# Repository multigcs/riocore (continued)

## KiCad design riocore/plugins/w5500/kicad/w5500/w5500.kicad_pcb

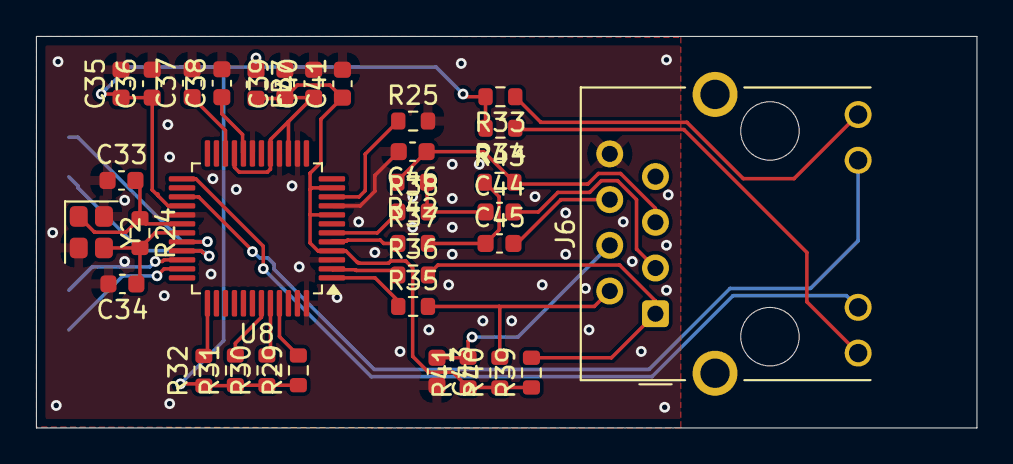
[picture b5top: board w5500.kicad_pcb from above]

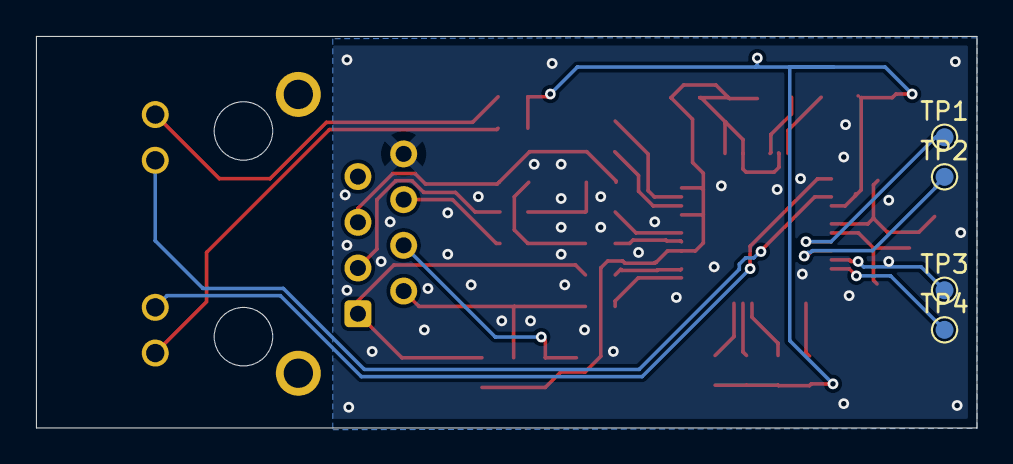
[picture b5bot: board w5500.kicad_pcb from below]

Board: 2 copper layers, 52.2 x 21.8 mm, 38 parts (4 on the bottom side), 32 nets.

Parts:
C33, C34: 18pF; C_0603_1608Metric
C35, C39: 10uF/6.3V; C_0603_1608Metric
C36, C40, C41: 0.1uF; C_0603_1608Metric
C37, C46: 10nF; C_0603_1608Metric
C38: 4.7uF; C_0603_1608Metric
C43: 22nF; C_0603_1608Metric
C44, C45: 6.8nF; C_0603_1608Metric
FB7: FB_100R_3A; L_0603_1608Metric
J6: RJ45_Pulse_J0011D21BNL; RJ45_Hanrun_HR911105A_Horizontal
R24: 1M; R_0603_1608Metric
R25: 12.4K; R_0603_1608Metric
R29, R30, R31, R32: 10K; R_0603_1608Metric
R33, R34: 330R; R_0603_1608Metric
R35, R36, R37, R38: 0R; R_0603_1608Metric
R39, R40, R42, R43: 49.9R; R_0603_1608Metric
R41: 10R; R_0603_1608Metric
TP1, TP2, TP3, TP4: TestPoint; TestPoint_Pad_D1.0mm
U8: W5500; LQFP-48_7x7mm_P0.5mm
Y2: Crystal_25MHz; Crystal_SMD_2520-4Pin_2.5x2.0mm

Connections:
+3V3: C35.1, C36.1, FB7.1, R29.1, R30.1, R31.1, R32.1, R33.2, R34.2, U8.28 (VDD)
/3V3_ADD: C39.1, C40.1, C41.1, FB7.2, R39.1, R40.1, R41.1, U8.4 (AVDD), U8.8 (AVDD), U8.11 (AVDD), U8.15 (AVDD), U8.17 (AVDD), U8.21 (AVDD)
/LED_GRN: J6.10, U8.25 (LINKLED)
/LED_YEL: J6.11, U8.27 (ACTLED)
/miso: TP3.1, U8.34 (MISO)
/mosi: TP4.1, U8.35 (MOSI)
/rst: R32.2, U8.37 (~RST)
/sclk: TP2.1, U8.33 (SCLK)
/sel: TP1.1, U8.32 (~SCS)
GND: C33.1, C34.2, C35.2, C36.2, C37.2, C38.2, C39.2, C40.2, C41.2, C43.2, C46.2, J6.8 (SH), R25.2, U8.3 (AGND), U8.9 (AGND), U8.14 (AGND), U8.16 (AGND), U8.19 (AGND), U8.29 (GND), U8.48 (AGND), Y2.2, Y2.4
unnamed: C44.1, R38.2, R42.1
unnamed: C45.1, R37.2, R43.1
unnamed: J6.9, R34.1
unnamed: J6.12, R33.1
unnamed: C46.1, J6.5 (RCT), R42.2, R43.2
unnamed: C44.2, J6.3 (RD+)
unnamed: C45.2, J6.6 (RD-)
unnamed: C43.1, J6.4 (TCT), R41.2
unnamed: J6.1 (TD+), R36.2, R39.2
unnamed: J6.2 (TD-), R35.2, R40.2
unnamed: C37.1, U8.22 (1V2O)
unnamed: R25.1, U8.10 (EXRES1)
unnamed: R29.2, U8.45 (PMODE0)
unnamed: R30.2, U8.44 (PMODE1)
unnamed: R31.2, U8.43 (PMODE2)
unnamed: R37.1, U8.5 (RXN)
unnamed: R38.1, U8.6 (RXP)
unnamed: C38.1, U8.20 (TOCAP)
unnamed: R35.1, U8.1 (TXN)
unnamed: R36.1, U8.2 (TXP)
unnamed: C33.2, R24.1, U8.30 (XI/CLKIN), Y2.1
unnamed: C34.1, R24.2, U8.31 (XO), Y2.3

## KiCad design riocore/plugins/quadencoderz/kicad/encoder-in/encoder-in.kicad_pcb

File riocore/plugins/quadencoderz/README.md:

# quadencoderz

**quadencoder with index pin**

usable as spindle-encoder for rigid tapping and thread cutting.  It is critical that your position-scale and QUAD_TYPE match, see the details in the description for QUAD_TYPE

* Keywords: feedback encoder rotary linear glassscale  index
* NEEDS: fpga

## Pins:
*FPGA-pins*
### a:

 * direction: input
 * pull: up

### b:

 * direction: input
 * pull: up

### z:
index pin

 * direction: input
 * pull: up

## Options:
*user-options*
### name:
name of this plugin instance

 * type: str
 * default: 

### image:
hardware type

 * type: imgselect
 * default: generic

### quad_type:
The count from the encoder will be bitshifted by the value of QUAD_TYPE.
Use 0 for 4x mode.  The position-scale should match.
For examle if you have a 600 CPR encoder 4x mode will give you 2400 PPR and your scale should be set to 2400.

 * type: int
 * min: 0
 * max: 4
 * default: 2

### rps_sum:
number of collected values before calculate the rps value

 * type: int
 * min: 0
 * max: 100
 * default: 10

## Signals:
*signals/pins in LinuxCNC*
### indexenable:

 * type: bit
 * direction: inout

### indexout:

 * type: bit
 * direction: input

### nocntreset:
set counter to zero on index in hardware

 * type: bit
 * direction: output

### position:
position feedback in steps

 * type: float
 * direction: input

### rps:
calculates revolutions per second

 * type: float
 * direction: input

### rpm:
calculates revolutions per minute

 * type: float
 * direction: input

## Interfaces:
*transport layer*
### indexenable:

 * size: 1 bit
 * direction: output

### indexout:

 * size: 1 bit
 * direction: input

### position:

 * size: 32 bit
 * direction: input

### nocntreset:

 * size: 1 bit
 * direction: output

## Verilogs:
 * [quadencoderz.v](quadencoderz.v)

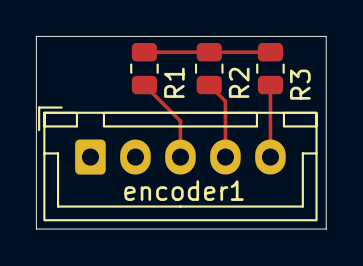
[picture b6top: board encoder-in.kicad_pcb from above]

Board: 2 copper layers, 16.1 x 10.7 mm, 4 parts (0 on the bottom side), 4 nets.

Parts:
R1, R2, R3: 10k; R_0805_2012Metric
encoder1: Conn_01x05; JST_XH_B5B-XH-A_1x05_P2.50mm_Vertical

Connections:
+3V3: R1.2, R2.2, R3.2
/a: R1.1, encoder1.3
/b: R2.1, encoder1.4
/z: R3.1, encoder1.5

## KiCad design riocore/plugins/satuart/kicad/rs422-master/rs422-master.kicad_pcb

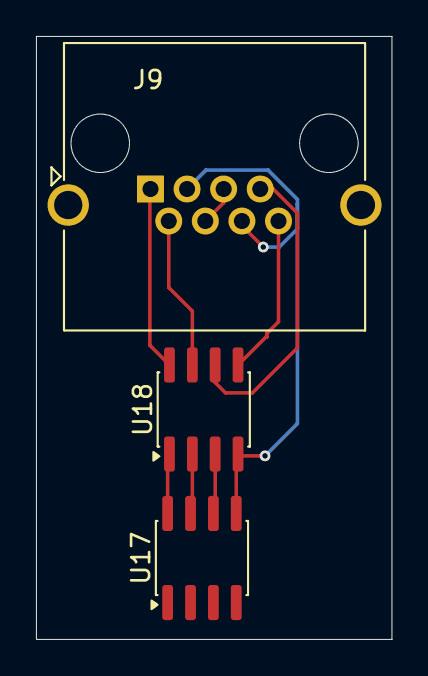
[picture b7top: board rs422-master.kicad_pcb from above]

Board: 2 copper layers, 19.8 x 33.5 mm, 3 parts (0 on the bottom side), 9 nets.

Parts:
J9: RJ45; RJ45_Amphenol_RJHSE5380
U17: ADuM1201BR; SOIC-8_3.9x4.9mm_P1.27mm
U18: ADM3488ExR; SOIC-8_3.9x4.9mm_P1.27mm

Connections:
F_5V: U17.8 (VDD2), U18.1 (VCC)
F_24V: J9.4, J9.5
F_GND: J9.3, J9.6, U17.5 (GND2), U18.4 (GND)
unnamed: U17.7 (VIA), U18.2 (RO)
unnamed: U17.6 (VOB), U18.3 (DI)
unnamed: J9.1, U18.8 (A)
unnamed: J9.2, U18.7 (B)
unnamed: J9.8, U18.5 (Y)
unnamed: J9.7, U18.6 (Z)

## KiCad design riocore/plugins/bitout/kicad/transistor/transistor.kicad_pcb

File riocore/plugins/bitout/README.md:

# bitout

**singe bit output pin**

to control relay, leds, valves, ....

* Keywords: led relais relay valve lamp motor magnet
* NEEDS: fpga

## Pins:
*FPGA-pins*
### bit:

 * direction: output

## Options:
*user-options*
### name:
name of this plugin instance

 * type: str
 * default: 

### image:
hardware type

 * type: imgselect
 * default: generic

## Signals:
*signals/pins in LinuxCNC*
### bit:

 * type: bit
 * direction: output

## Interfaces:
*transport layer*
### bit:

 * size: 1 bit
 * direction: output

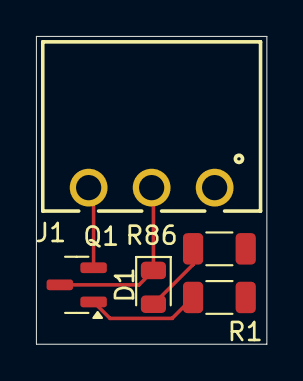
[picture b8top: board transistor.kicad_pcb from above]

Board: 2 copper layers, 12.8 x 17.1 mm, 5 parts (0 on the bottom side), 4 nets.

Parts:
D1: LED; LED_0805_2012Metric
J1: bit_out; 691322110003
Q1: BC817; SOT-23
R1: 1k; R_1206_3216Metric
R86: 560; R_1206_3216Metric

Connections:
GND: J1.3, Q1.2 (E)
unnamed: D1.2 (A), R86.2
unnamed: D1.1 (K), J1.2, Q1.3 (C)
unnamed: Q1.1 (B), R1.2

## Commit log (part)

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2026-04-25 kicad: adding offsets
2026-04-25 kicad: using rendered images
2026-04-25 flow: fixing generic image view
2026-04-25 flow: icons
2026-04-25 kicad: adding pico module / encoder
2026-04-25 kicad: per board filtering
2026-04-27 kicad: stepstick module
2026-04-27 kicad: renew some uuids
2026-04-27 kicad: spi-connector module
2026-04-27 kicad: encoder-in module
2026-04-27 some changes
2026-04-27 some fixes
2026-04-29 kicad: ecp5 tests
2026-05-06 flow: fixing edge delete
2026-05-11 modifiers: add only used verilogs
2026-05-11 ISE: using single verilog files and xst-file
2026-05-11 ISE: experimental cpld support / adding XC9536XL board
2026-05-11 ruff: activate B006
2026-05-11 ruff: activate PLR1733, RUF100
2026-05-11 ruff: activate PYI061,RUF059,PLR1714
2026-05-11 ruff: activate RET501,RET502
2026-05-11 ruff: activate SIM102
2026-05-11 jog: some fixes
2026-05-11 jog: scale mode
2026-05-11 jog: add vcp status
2026-05-12 fixing tests
2026-05-12 adding halview tool
2026-05-12 halview: better labels
2026-05-13 kicad: breakout
2026-05-13 halgraph: some fixes (thanks to miniwini)
2026-05-13 halgraph: adding color support
2026-05-13 halgraph: better in/out check
2026-05-13 halgraph: sorted pins
2026-05-13 makefile
2026-05-13 fpga: fixing xc9500xl build
2026-05-14 halview: using QGraphicsScene
2026-05-14 typo
2026-05-14 halview: using halcmd to generate the graph
2026-05-18 some RPI5 - SPI fixes
2026-05-18 set rpi5 spi mode while converting old configs
2026-05-18 axis sorting / empty functions
2026-05-18 component: fixing some warning
2026-05-19 better config upgrade/convert
2026-05-19 flow: no default image
2026-05-19 generator: try to load tnc module
2026-05-19 flow: hover info
2026-05-19 flow: better 'nesting'
2026-05-19 flow: nesting: modifiers
2026-05-19 flow: nesting
2026-05-21 flow: using graphvis
2026-05-21 stepdir: fixing divider (big thanks to Tim Bee)
2026-05-22 modifiers: fixing names to find the files (thanks to Tim Bee)
2026-05-26 generator: little fixes
2026-05-27 rpiio: wizard
2026-05-27 serial: error msg
2026-05-27 hal: add_halcomp
2026-05-27 ise: readding flash cmd
2026-05-28 adding paport sim script
2026-05-28 hal: adding iocontrol.0.emc-enable-in/motion.enable overwrites
